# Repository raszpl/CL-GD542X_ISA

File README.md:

Fork of https://github.com/matt1187/542x_ISA 'Remaking from Cirrus Logic Databook "CL-GD542X_Technical_Reference_Manual_Jan1994"' attempting to show some routing optimizations.

# Results

Original:

Optimisations, less and taking smaller area tracks you see on the back means better signal integrity.

Initial:

Final:

Comparison between layouts: [Original](/images/original.png?raw=true), [Initial optimization](/images/first.png?raw=true), [Final version](/images/final.png?raw=true).

Black holes and red are cuts in ground plane, the smaller they are the better. Ideally you want one uninterrupted plane. Second bad but better than nothing option is ground island densely stitched on top of tracks forced to go into ground plane. Third bad option is as short as possible cuts to the ground plane and picking slow/steady (reset, VCC) signals as the ones going across, jumping across couple signals here and there is a lesser crime than slicing ground across half the PCB height. Fourth 'Im desperate here' option is crossing signals at 90 degree angle and hoping PCB thickness is enough. People in the eighties and early nineties didnt have it easy, nowadays similar size 4-layer PCBs are mere $20-30 for quick turnaround pototypes, with 6-layer not far behind at $40!

# Fixes

1 Bad ground. We dont want thin long ground noodles connected to real ground by a thin sliver on one side

like between:
- PD0 PD1 PD2 PD3 PD4 PD5 PD6
- PD16 20 21 22 23
- under U5
- tiny one under U11
- long big one under extended ISA slot
- A2_ISA 3 4 5 6 7

Ground that is not solid plane or densely (<wavelenght) stitched to solid plane no longer works as ground, it works like an antenna and amplifies interference. In the past guard traces were used before we had good modeling and understanding of magnetic propagation on the pcb, they only worked because putting one forced engineers to make more space between signal traces. All those dangling traces between signal tracks just resonate amplifying interference[^1].

3 Extended ISA slot - routing VCC straight to C33 instead of going across the card wouldnt be breaking ground plane under D8-16 and LA signals.

4 Omitting ISA oscillator input option will make ground more solid. Currently it leaves a dangling track with very high frequency clock crossing D8-18 and LA lines while breaking ground even when unused. Using ISA 14MHz was a cost cutting measure saving maybe 50 cents for a crystal resonator and two capacitors in the nineties, nowadays useless.

5 Pin 159 oscillator goes in a weird around pad way making it go outside of ground plane coverage. Its especially critical to have uninterrupted ground under clock signals.

6 Afaik separate isolated analog/digital ground planes is a relic of the past, modern techniques show it doesnt work if it cuts up ground into multiple islands and forces signals to cross them[^2][^3][^4]. Here for example it paradoxically messes with analog signal integrity by making RGB Video suddenly lose reference. Im fairly certain this aspect of Cirrus recommended design only makes things worse.

7 Optional EEprom pins also degrade analog RGB Video signals by breaking ground :( best option would be routing those two tracks with jumpers over analog RGB.

8 Filtering analog VGA looks nice when symmetricaly placed in neat rows, but forces analog B crossing over analog G, and all analog tracks going under where they arent routed over ground plane. Vias high impedance is really bad for such high speed analog signals. Asymmetrical component placement might hurt OCD, but lets us leave Analog RGB on top layer over healthy uninterrupted ground.

9 H and V syncs cross each other with no ground underneath, swapping filtering sections around solves that.

10 3 amp fuse and thick tracks on Vga Pin 9 is overdoing it, especially considering Cirrus is not even capable of reading Edid. Removing altogether.

11 Very long RAS1 under U13 U14 can be avoided, makes it look stupid but ground plane is healthier = shorter cuts = shorter return paths = less interference and crosstalk.

TLDR Golden rule is every signal should run as close as possible (preferably over) a ground directly connecting source and destination of said signal with lowest impedance. Signals arent electrons, they are electromagnetic waves and need to close the loop. Closer the ground smaller the field, lower the ground impedance higher the frequency of mitigated interferences, bigger ground plane = better, traveling thru multiple vias = bad.

Some of the fixes are heavily overdoing it via stitched ground patches and are most likely also bad :) Nowadays upgrading from five PCBs with 2-layers to 4-layers of that size is $20, another $15 for 6-layer with ENIG finish, giving us infinitely healthier signal integrity and tons less routing work. __Please dont manufacture this!__ Other than for fun or experimentation there is very little sense manufacturing 2-layer design, repository is for educational purposes only.

# License
The project is free for non-commercial reproduction. Do not sell it on Ebay or other platforms for profit. Do not make a closed source derivative. Share your experiences and ideas with the community.

This work is licensed under a [Creative Commons Attribution-NonCommercial-ShareAlike 4.0 International License][cc-by-nc-sa].

[![CC BY-NC-SA 4.0][cc-by-nc-sa-image]][cc-by-nc-sa]

[cc-by-nc-sa]: http://creativecommons.org/licenses/by-nc-sa/4.0/
[cc-by-nc-sa-image]: https://licensebuttons.net/l/by-nc-sa/4.0/88x31.png

# References
[^1]: https://resources.altium.com/p/guard-traces-hit-or-myth.
[^2]: https://resources.altium.com/p/how-to-use-a-star-point-for-analog-ground-digital-ground-connection
[^3]: https://resources.pcb.cadence.com/blog/2021-should-you-ever-separate-analog-and-digital-ground-planes
[^4]: "Ground planes in a PCB layout with 30 years of experience: The ultimate guide" by Hans Rosenberg https://www.youtube.com/watch?v=EEb_0dja8tE&list=PLsWHPs7La-3KUY2JDUyrz0Jc0xw8kH4zQ

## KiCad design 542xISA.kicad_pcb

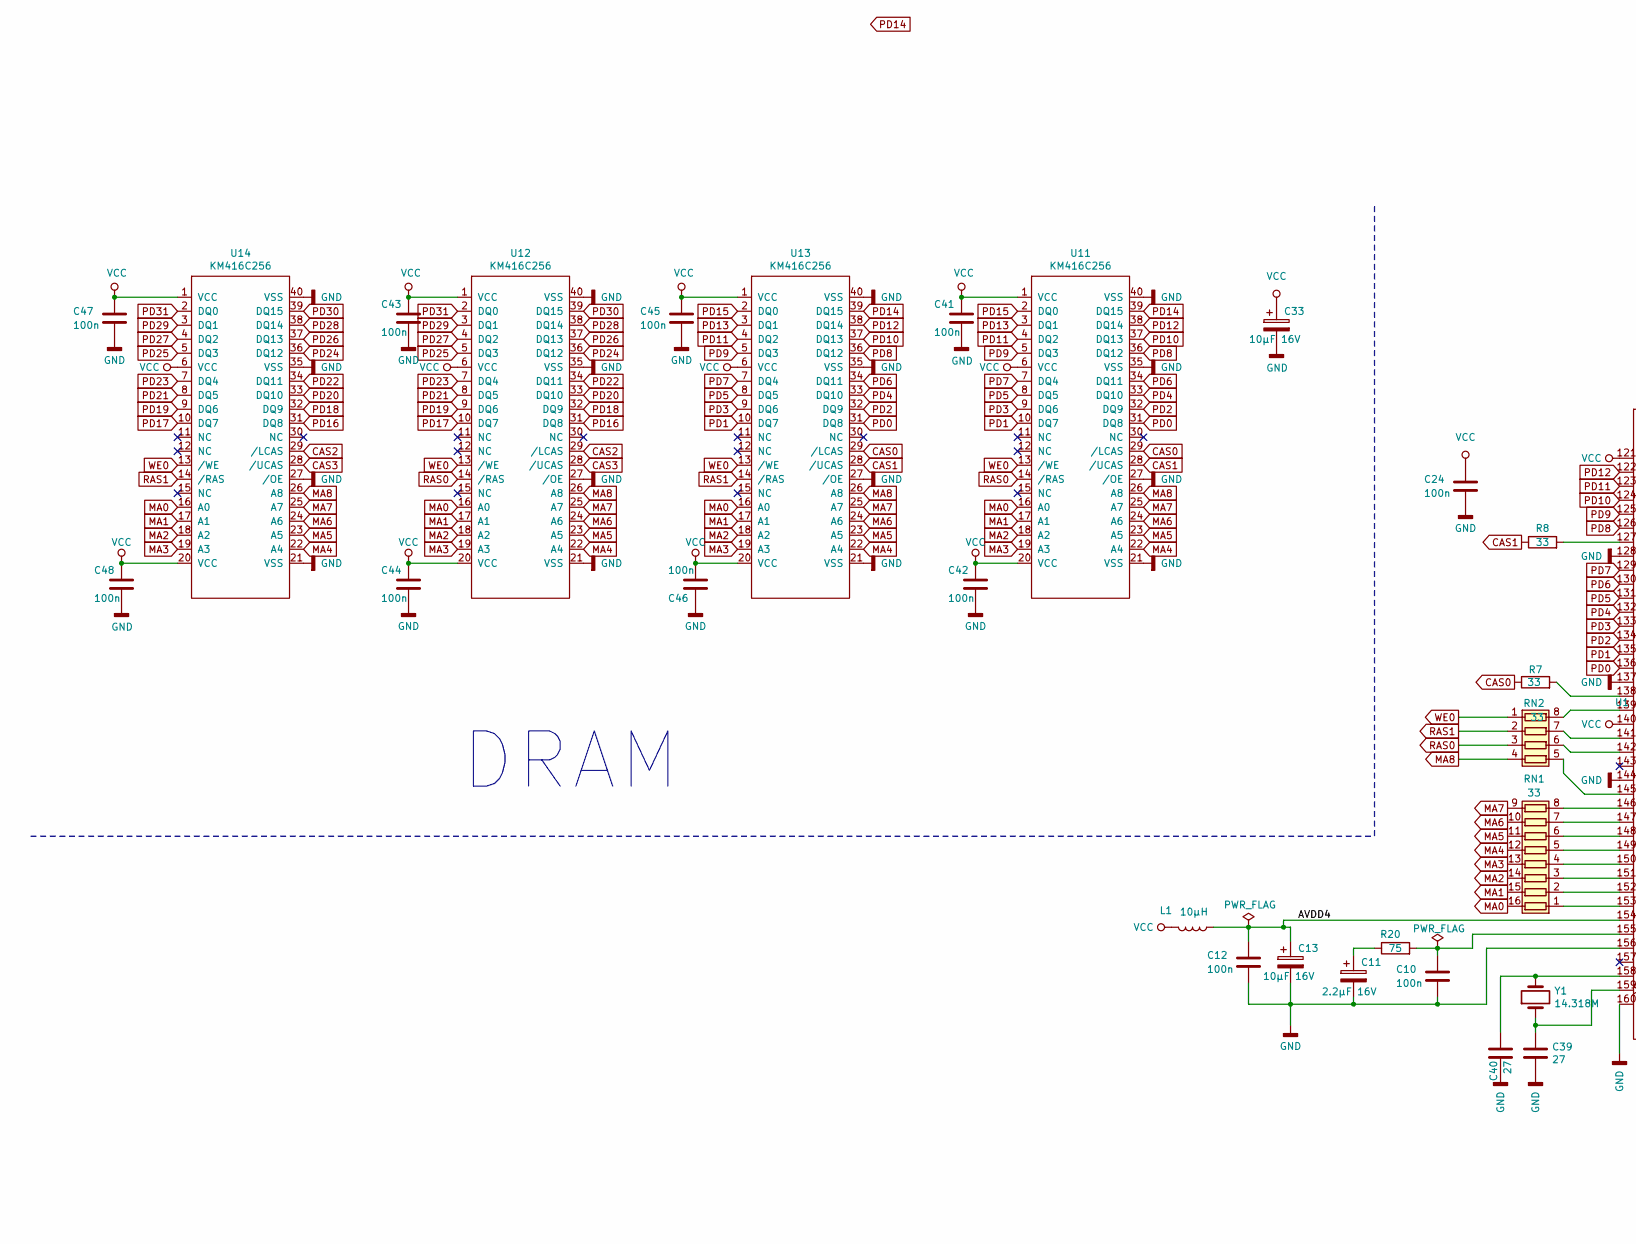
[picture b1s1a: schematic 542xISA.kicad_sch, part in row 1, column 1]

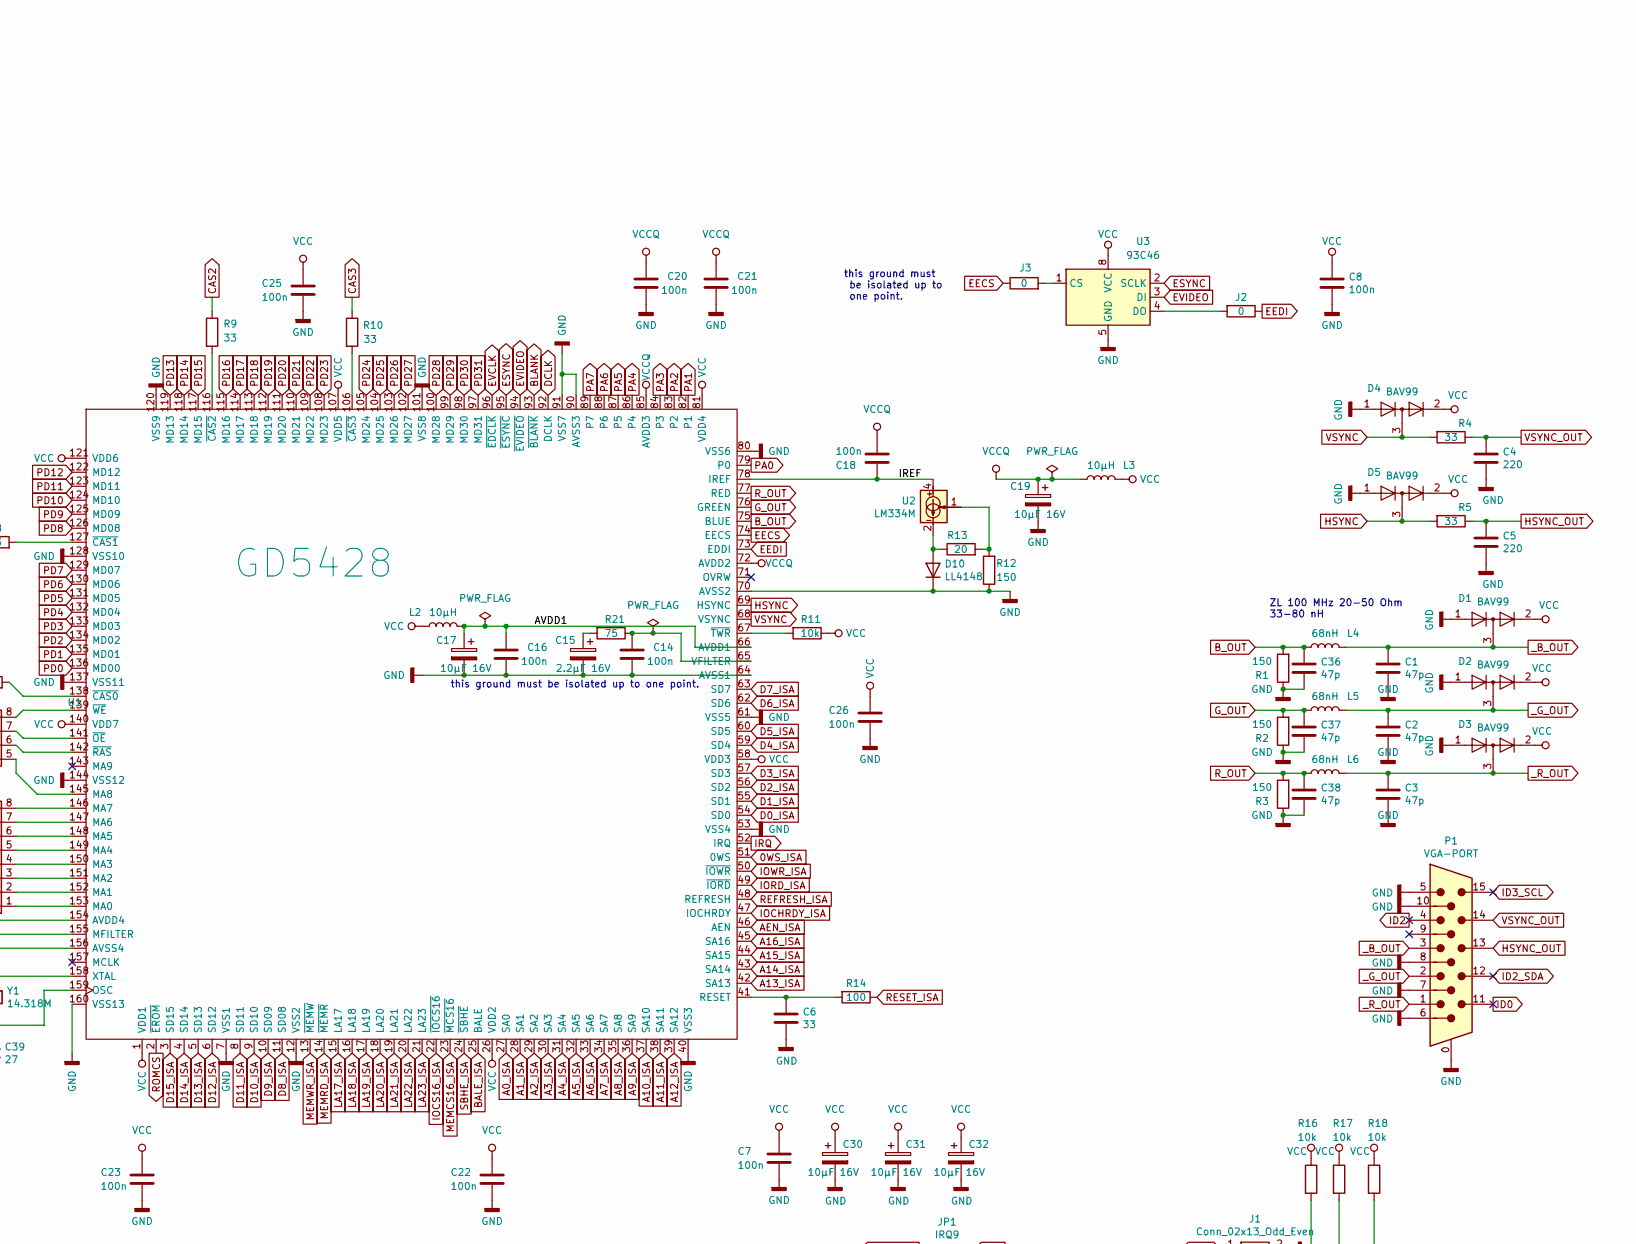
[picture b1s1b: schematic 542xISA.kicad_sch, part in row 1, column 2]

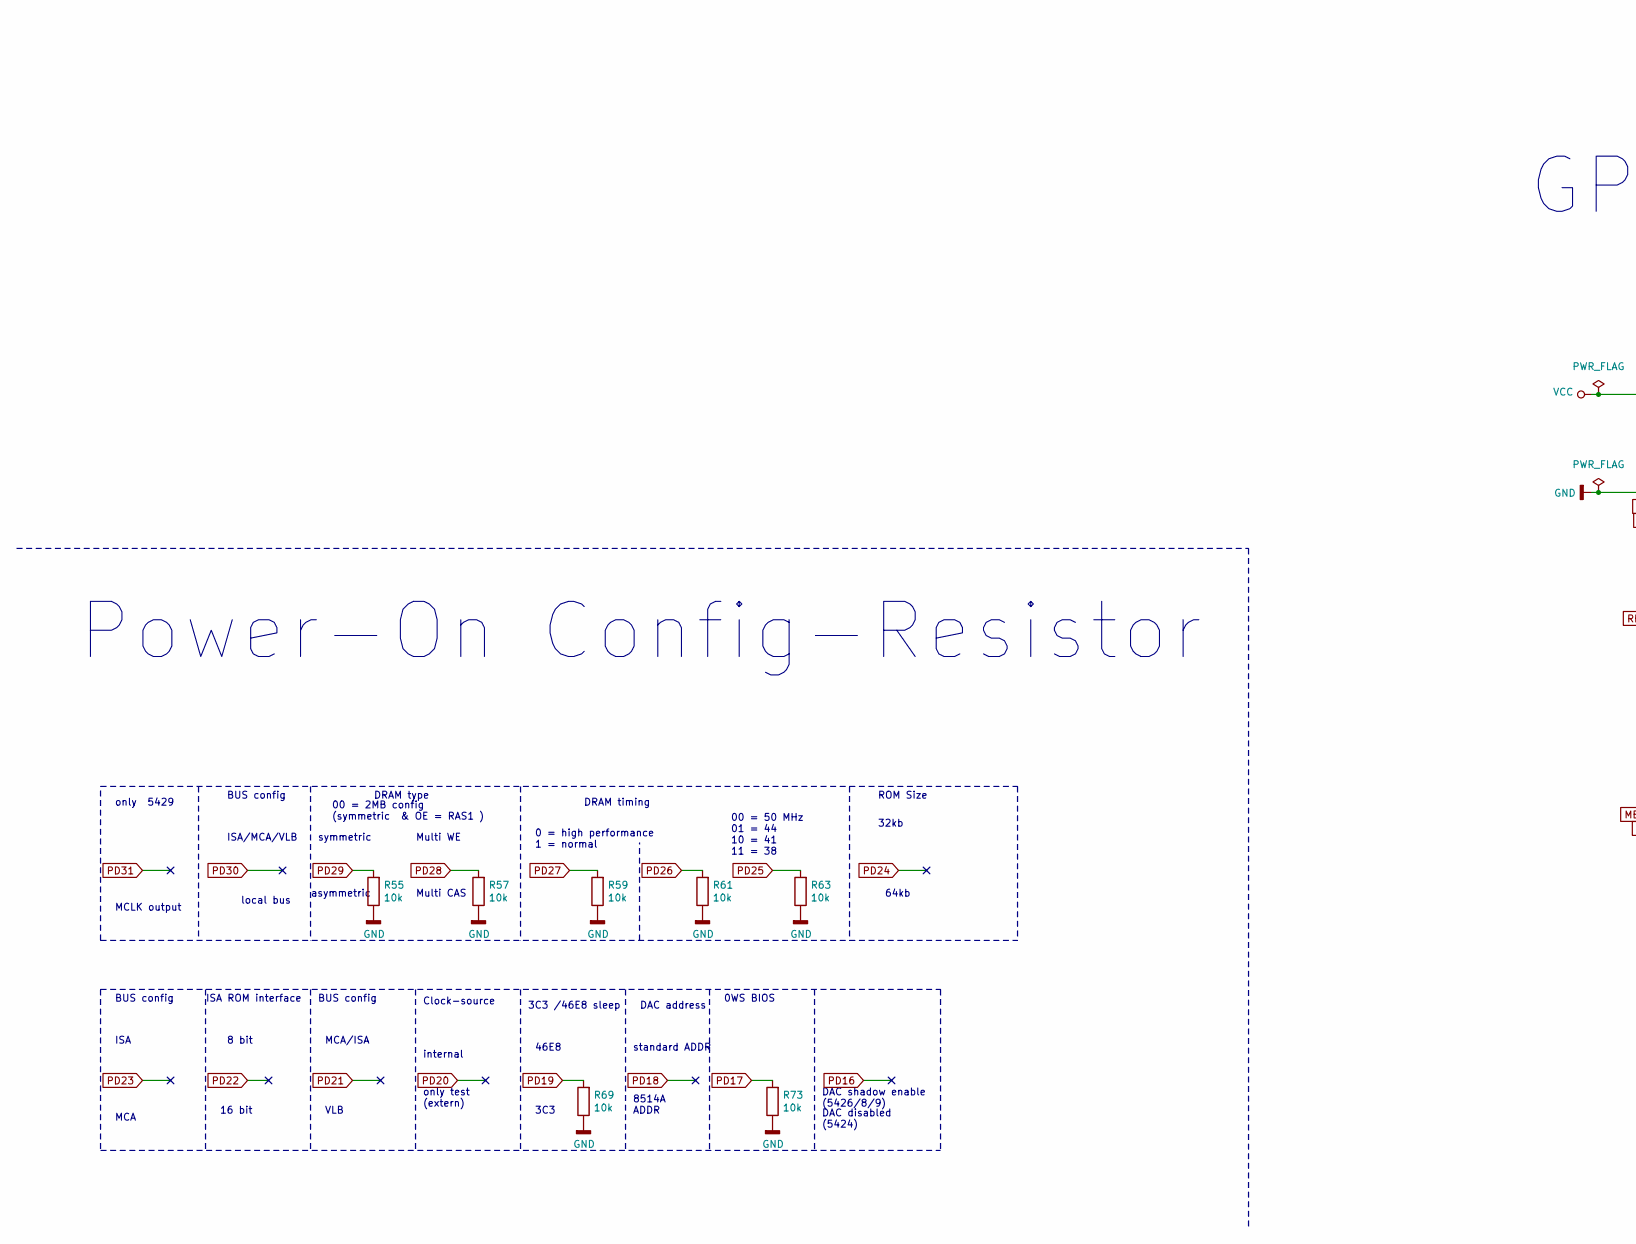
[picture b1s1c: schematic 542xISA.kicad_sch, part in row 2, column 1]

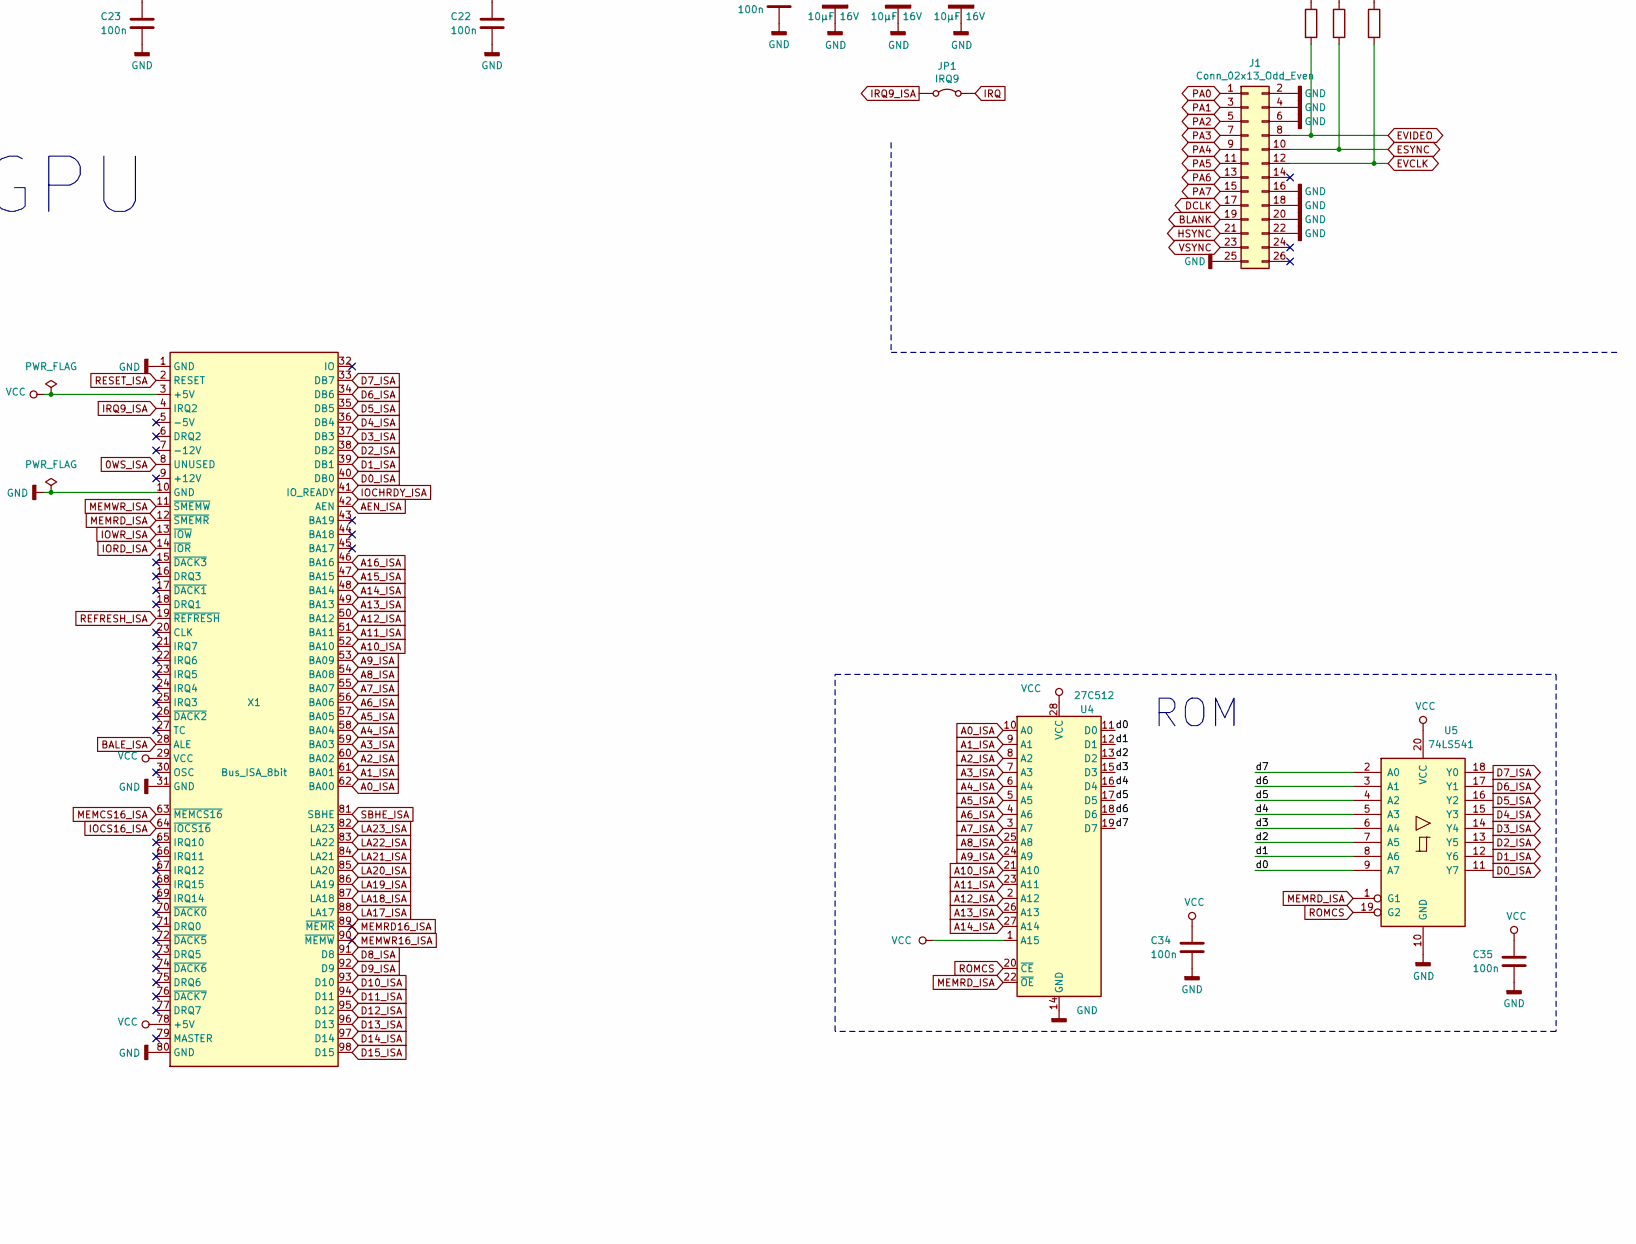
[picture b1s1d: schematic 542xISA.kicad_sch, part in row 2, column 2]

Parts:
C1, C2, C3, C36, C37, C38: 47p; C_0805_2012Metric
C4, C5: 220; C_0805_2012Metric
C6: 33; C_0805_2012Metric
C7, C8, C10, C12, C14, C16, C18, C20, C21, C22, C23, C24, C25, C26, C34, C35, C41, C42, C43, C44, C45, C46, C47, C48: 100n; C_0805_2012Metric
C11, C15: 2.2µF 16V; CP_EIA-3528-12_Kemet-T
C13, C17, C19, C30, C31, C32, C33: 10µF 16V; CP_EIA-6032-15_Kemet-U
C39, C40: 27; C_0805_2012Metric
D1, D2, D3, D4, D5: BAV99; SOT-23_Handsoldering
D10: LL4148; D_MiniMELF
J1: Conn_02x13_Odd_Even; PinHeader_2x13_P2.54mm_Vertical
J2, J3: 0; L_1806_4516Metric_Pad1.45x1.90mm_HandSolder
JP1: IRQ9; PinHeader_1x02_P2.54mm_Vertical
L1, L2: 10µH; L_0805_2012Metric
L3: 10µH; L_1206_3216Metric
L4, L5, L6: 68nH; L_1206_3216Metric
P1: VGA-PORT; DSUB-15-HD_Female_Horizontal_P2.29x1.98mm_EdgePinOffset8.35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
R1, R2, R3, R12: 150; R_0805_2012Metric
R4, R5, R7, R8, R9, R10: 33; R_0805_2012Metric
R11, R16, R17, R18, R55, R57, R59, R61, R63, R69, R73: 10k; R_0805_2012Metric
R13: 20; R_0805_2012Metric
R14: 100; R_0805_2012Metric
R20, R21: 75; R_0805_2012Metric
RN1: 33; R_Array_Convex_8x0602
RN2: 33; R_Array_Concave_4x0603
U1: GD5428; PQFP-160_28x28mm_P0.65mm
U2: LM334M; SOIC-8_3.9x4.9mm_P1.27mm
U3: 93C46; SOIC-8_3.9x4.9mm_P1.27mm
U4: 27C512; DIP-28_W15.24mm_Socket
U5: 74LS541; SOIC-20W_7.5x12.8mm_P1.27mm
U11, U12, U13, U14: KM416C256; SOJ-40-Socket-LongPads
X1: Bus_ISA_8bit; BUS_AT
Y1: 14.318M; Crystal_SMD_0603-2Pin_6.0x3.5mm

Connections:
0WS_ISA: U1.51 (0WS), X1.8 (UNUSED)
/AVDD1: C16.1, C17.1, L2.2, U1.66 (AVDD1)
/AVDD4: C12.1, C13.1, L1.1, U1.154 (AVDD4)
/IREF: C18.1, U1.78 (IREF), U2.4
/d0: U4.11 (D0), U5.9 (A7)
/d1: U4.12 (D1), U5.8 (A6)
/d2: U4.13 (D2), U5.7 (A5)
/d3: U4.15 (D3), U5.6 (A4)
/d4: U4.16 (D4), U5.5 (A3)
/d5: U4.17 (D5), U5.4 (A2)
/d6: U4.18 (D6), U5.3 (A1)
/d7: U4.19 (D7), U5.2 (A0)
A0_ISA: U1.27 (SA0), U4.10 (A0), X1.62 (BA00)
A1_ISA: U1.28 (SA1), U4.9 (A1), X1.61 (BA01)
A2_ISA: U1.29 (SA2), U4.8 (A2), X1.60 (BA02)
A3_ISA: U1.30 (SA3), U4.7 (A3), X1.59 (BA03)
A4_ISA: U1.31 (SA4), U4.6 (A4), X1.58 (BA04)
A5_ISA: U1.32 (SA5), U4.5 (A5), X1.57 (BA05)
A6_ISA: U1.33 (SA6), U4.4 (A6), X1.56 (BA06)
A7_ISA: U1.34 (SA7), U4.3 (A7), X1.55 (BA07)
A8_ISA: U1.35 (SA8), U4.25 (A8), X1.54 (BA08)
A9_ISA: U1.36 (SA9), U4.24 (A9), X1.53 (BA09)
A10_ISA: U1.37 (SA10), U4.21 (A10), X1.52 (BA10)
A11_ISA: U1.38 (SA11), U4.23 (A11), X1.51 (BA11)
A12_ISA: U1.39 (SA12), U4.2 (A12), X1.50 (BA12)
A13_ISA: U1.42 (SA13), U4.26 (A13), X1.49 (BA13)
A14_ISA: U1.43 (SA14), U4.27 (A14), X1.48 (BA14)
A15_ISA: U1.44 (SA15), X1.47 (BA15)
A16_ISA: U1.45 (SA16), X1.46 (BA16)
AEN_ISA: U1.46 (AEN), X1.42 (AEN)
BALE_ISA: U1.25 (BALE), X1.28 (ALE)
BLANK: J1.19, U1.93 (~BLANK)
B_OUT: C36.1, L4.2, R1.2, U1.75 (BLUE)
CAS0: R7.1, U11.29 (/LCAS), U13.29 (/LCAS)
CAS1: R8.1, U11.28 (/UCAS), U13.28 (/UCAS)
CAS2: R9.1, U12.29 (/LCAS), U14.29 (/LCAS)
CAS3: R10.1, U12.28 (/UCAS), U14.28 (/UCAS)
D0_ISA: U1.54 (SD0), U5.11 (Y7), X1.40 (DB0)
D1_ISA: U1.55 (SD1), U5.12 (Y6), X1.39 (DB1)
D2_ISA: U1.56 (SD2), U5.13 (Y5), X1.38 (DB2)
D3_ISA: U1.57 (SD3), U5.14 (Y4), X1.37 (DB3)
D4_ISA: U1.59 (SD4), U5.15 (Y3), X1.36 (DB4)
D5_ISA: U1.60 (SD5), U5.16 (Y2), X1.35 (DB5)
D6_ISA: U1.62 (SD6), U5.17 (Y1), X1.34 (DB6)
D7_ISA: U1.63 (SD7), U5.18 (Y0), X1.33 (DB7)
D8_ISA: U1.11 (SD08), X1.91 (D8)
D9_ISA: U1.10 (SD09), X1.92 (D9)
D10_ISA: U1.9 (SD10), X1.93 (D10)
D11_ISA: U1.8 (SD11), X1.94 (D11)
D12_ISA: U1.6 (SD12), X1.95 (D12)
D13_ISA: U1.5 (SD13), X1.96 (D13)
D14_ISA: U1.4 (SD14), X1.97 (D14)
D15_ISA: U1.3 (SD15), X1.98 (D15)
DCLK: J1.17, U1.92 (DCLK)
EECS: J3.1, U1.74 (EECS)
EEDI: J2.1, U1.73 (EDDI)
ESYNC: J1.10, R17.2, U1.95 (~ESYNC), U3.2 (SCLK)
EVCLK: J1.12, R18.2, U1.96 (~EDCLK)
EVIDEO: J1.8, R16.2, U1.94 (~EVIDEO), U3.3 (DI)
GND: C1.2, C2.2, C3.2, C4.2, C5.2, C6.2, C7.2, C8.2, C10.2, C11.2, C12.2, C13.2, C14.2, C15.2, C16.2, C17.2, C19.2, C20.2, C21.2, C22.2, C23.2, C24.2, C25.2, C26.2, C30.2, C31.2, C32.2, C33.2, C34.2, C35.2, C36.2, C37.2, C38.2, C39.2, C40.1, C41.2, C42.2, C43.2, C44.2, C45.2, C46.2, C47.2, C48.2, D1.1 (K), D2.1 (K), D3.1 (K), D4.1 (K), D5.1 (K), D10.1 (K), J1.2, J1.4, J1.6, J1.16, J1.18, J1.20, J1.22, J1.25, P1.0, P1.5, P1.6, P1.7, P1.8, P1.10, R1.1, R2.1, R3.1, R12.1, R55.1, R57.1, R59.1, R61.1, R63.1, R69.1, R73.1, U1.7 (VSS1), U1.12 (VSS2), U1.40 (VSS3), U1.53 (VSS4), U1.61 (VSS5), U1.64 (AVSS1), U1.70 (AVSS2), U1.80 (VSS6), U1.90 (AVSS3), U1.91 (VSS7), U1.101 (VSS8), U1.120 (VSS9), U1.128 (VSS10), U1.137 (VSS11), U1.144 (VSS12), U1.156 (AVSS4), U1.160 (VSS13), U3.5 (GND), U4.14 (GND), U5.10 (GND), U11.21 (VSS), U11.27 (/OE), U11.35 (VSS), U11.40 (VSS), U12.21 (VSS), U12.27 (/OE), U12.35 (VSS), U12.40 (VSS), U13.21 (VSS), U13.27 (/OE), U13.35 (VSS), U13.40 (VSS), U14.21 (VSS), U14.27 (/OE), U14.35 (VSS), U14.40 (VSS), X1.1 (GND), X1.10 (GND), X1.31 (GND), X1.80 (GND)
G_OUT: C37.1, L5.2, R2.2, U1.76 (GREEN)
HSYNC: D5.3 (K), J1.21, R5.2, U1.69 (HSYNC)
HSYNC_OUT: C5.1, P1.13, R5.1
ID0: P1.11
ID2: P1.4
ID2_SDA: P1.12
ID3_SCL: P1.15
IOCHRDY_ISA: U1.47 (IOCHRDY), X1.41 (IO_READY)
IOCS16_ISA: U1.22 (~IOCS16), X1.64 (~IOCS16)
IORD_ISA: U1.49 (~IORD), X1.14 (~IOR)
IOWR_ISA: U1.50 (~IOWR), X1.13 (~IOW)
IRQ: JP1.2 (B), U1.52 (IRQ)
IRQ9_ISA: JP1.1 (A), X1.4 (IRQ2)
LA17_ISA: U1.15 (LA17), X1.88 (LA17)
LA18_ISA: U1.16 (LA18), X1.87 (LA18)
LA19_ISA: U1.17 (LA19), X1.86 (LA19)
LA20_ISA: U1.18 (LA20), X1.85 (LA20)
LA21_ISA: U1.19 (LA21), X1.84 (LA21)
LA22_ISA: U1.20 (LA22), X1.83 (LA22)
LA23_ISA: U1.21 (LA23), X1.82 (LA23)
MA0: RN1.16 (R1.2), U11.16 (A0), U12.16 (A0), U13.16 (A0), U14.16 (A0)
MA1: RN1.15 (R2.2), U11.17 (A1), U12.17 (A1), U13.17 (A1), U14.17 (A1)
MA2: RN1.14 (R3.2), U11.18 (A2), U12.18 (A2), U13.18 (A2), U14.18 (A2)
MA3: RN1.13 (R4.2), U11.19 (A3), U12.19 (A3), U13.19 (A3), U14.19 (A3)
MA4: RN1.12 (R5.2), U11.22 (A4), U12.22 (A4), U13.22 (A4), U14.22 (A4)
MA5: RN1.11 (R6.2), U11.23 (A5), U12.23 (A5), U13.23 (A5), U14.23 (A5)
MA6: RN1.10 (R7.2), U11.24 (A6), U12.24 (A6), U13.24 (A6), U14.24 (A6)
MA7: RN1.9 (R8.2), U11.25 (A7), U12.25 (A7), U13.25 (A7), U14.25 (A7)
MA8: RN2.4 (R4.1), U11.26 (A8), U12.26 (A8), U13.26 (A8), U14.26 (A8)
MEMCS16_ISA: U1.23 (~MCS16), X1.63 (~MEMCS16)
MEMRD16_ISA: X1.89 (~MEMR)
MEMRD_ISA: U1.14 (~MEMR), U4.22 (~OE), U5.1 (G1), X1.12 (~SMEMR)
MEMWR16_ISA: X1.90 (~MEMW)
MEMWR_ISA: U1.13 (~MEMW), X1.11 (~SMEMW)
unnamed: C11.1, R20.1
unnamed: C15.1, R21.2
unnamed: D10.2 (A), R13.1, U2.2, U2.3, U2.6, U2.7
unnamed: R12.2, R13.2, U2.1
unnamed: RN1.1 (R1.1), U1.153 (MA0)
unnamed: RN1.2 (R2.1), U1.152 (MA1)
unnamed: RN1.3 (R3.1), U1.151 (MA2)
unnamed: RN1.4 (R4.1), U1.150 (MA3)
unnamed: RN1.5 (R5.1), U1.149 (MA4)
unnamed: RN1.6 (R6.1), U1.148 (MA5)
unnamed: RN1.7 (R7.1), U1.147 (MA6)
unnamed: RN1.8 (R8.1), U1.146 (MA7)
unnamed: RN2.8 (R1.2), U1.139 (~WE)
unnamed: RN2.7 (R2.2), U1.141 (~OE)
unnamed: RN2.6 (R3.2), U1.142 (~RAS)
unnamed: RN2.5 (R4.2), U1.145 (MA8)
unnamed: C10.1, R20.2, U1.155 (MFILTER)
unnamed: C39.1, U1.159 (OSC), Y1.1
unnamed: C6.1, R14.2, U1.41 (RESET)
unnamed: C14.1, R21.1, U1.65 (VFILTER)
unnamed: C40.2, U1.158 (XTAL), Y1.2
unnamed: R7.2, U1.138 (~CAS0)
unnamed: R8.2, U1.127 (~CAS1)
unnamed: R9.2, U1.116 (~CAS2)
unnamed: R10.2, U1.106 (~CAS3)
unnamed: R11.2, U1.67 (~TWR)
unnamed: J3.2, U3.1 (CS)
unnamed: J2.2, U3.4 (DO)
PA0: J1.1, U1.79 (P0)
PA1: J1.3, U1.82 (P1)
PA2: J1.5, U1.83 (P2)
PA3: J1.7, U1.84 (P3)
PA4: J1.9, U1.86 (P4)
PA5: J1.11, U1.87 (P5)
PA6: J1.13, U1.88 (P6)
PA7: J1.15, U1.89 (P7)
PD0: U1.136 (MD00), U11.31 (DQ8), U13.31 (DQ8)
PD1: U1.135 (MD01), U11.10 (DQ7), U13.10 (DQ7)
PD2: U1.134 (MD02), U11.32 (DQ9), U13.32 (DQ9)
PD3: U1.133 (MD03), U11.9 (DQ6), U13.9 (DQ6)
PD4: U1.132 (MD04), U11.33 (DQ10), U13.33 (DQ10)
PD5: U1.131 (MD05), U11.8 (DQ5), U13.8 (DQ5)
PD6: U1.130 (MD06), U11.34 (DQ11), U13.34 (DQ11)
PD7: U1.129 (MD07), U11.7 (DQ4), U13.7 (DQ4)
PD8: U1.126 (MD08), U11.36 (DQ12), U13.36 (DQ12)
PD9: U1.125 (MD09), U11.5 (DQ3), U13.5 (DQ3)
PD10: U1.124 (MD10), U11.37 (DQ13), U13.37 (DQ13)
PD11: U1.123 (MD11), U11.4 (DQ2), U13.4 (DQ2)
PD12: U1.122 (MD12), U11.38 (DQ14), U13.38 (DQ14)
PD13: U1.119 (MD13), U11.3 (DQ1), U13.3 (DQ1)
PD14: U1.118 (MD14), U11.39 (DQ15), U13.39 (DQ15)
PD15: U1.117 (MD15), U11.2 (DQ0), U13.2 (DQ0)
PD16: U1.115 (MD16), U12.31 (DQ8), U14.31 (DQ8)
PD17: R73.2, U1.114 (MD17), U12.10 (DQ7), U14.10 (DQ7)
PD18: U1.113 (MD18), U12.32 (DQ9), U14.32 (DQ9)
PD19: R69.2, U1.112 (MD19), U12.9 (DQ6), U14.9 (DQ6)
PD20: U1.111 (MD20), U12.33 (DQ10), U14.33 (DQ10)
PD21: U1.110 (MD21), U12.8 (DQ5), U14.8 (DQ5)
PD22: U1.109 (MD22), U12.34 (DQ11), U14.34 (DQ11)
PD23: U1.108 (MD23), U12.7 (DQ4), U14.7 (DQ4)
PD24: U1.105 (MD24), U12.36 (DQ12), U14.36 (DQ12)
PD25: R63.2, U1.104 (MD25), U12.5 (DQ3), U14.5 (DQ3)
PD26: R61.2, U1.103 (MD26), U12.37 (DQ13), U14.37 (DQ13)
PD27: R59.2, U1.102 (MD27), U12.4 (DQ2), U14.4 (DQ2)
PD28: R57.2, U1.100 (MD28), U12.38 (DQ14), U14.38 (DQ14)
PD29: R55.2, U1.99 (MD29), U12.3 (DQ1), U14.3 (DQ1)
PD30: U1.98 (MD30), U12.39 (DQ15), U14.39 (DQ15)
PD31: U1.97 (MD31), U12.2 (DQ0), U14.2 (DQ0)
RAS0: RN2.3 (R3.1), U11.14 (/RAS), U12.14 (/RAS)
RAS1: RN2.2 (R2.1), U13.14 (/RAS), U14.14 (/RAS)
REFRESH_ISA: U1.48 (REFRESH), X1.19 (~REFRESH)
RESET_ISA: R14.1, X1.2 (RESET)
ROMCS: U1.2 (~EROM), U4.20 (~CE), U5.19 (G2)
R_OUT: C38.1, L6.2, R3.2, U1.77 (RED)
SBHE_ISA: U1.24 (~SBHE), X1.81 (SBHE)
VCC: C7.1, C8.1, C22.1, C23.1, C24.1, C25.1, C26.1, C30.1, C31.1, C32.1, C33.1, C34.1, C35.1, C41.1, C42.1, C43.1, C44.1, C45.1, C46.1, C47.1, C48.1, D1.2 (A), D2.2 (A), D3.2 (A), D4.2 (A), D5.2 (A), L1.2, L2.1, L3.1, R11.1, R16.1, R17.1, R18.1, U1.1 (VDD1), U1.26 (VDD2), U1.58 (VDD3), U1.81 (VDD4), U1.107 (VDD5), U1.121 (VDD6), U1.140 (VDD7), U3.8 (VCC), U4.1 (A15), U4.28 (VCC), U5.20 (VCC), U11.1 (VCC), U11.6 (VCC), U11.20 (VCC), U12.1 (VCC), U12.6 (VCC), U12.20 (VCC), U13.1 (VCC), U13.6 (VCC), U13.20 (VCC), U14.1 (VCC), U14.6 (VCC), U14.20 (VCC), X1.3 (+5V), X1.29 (VCC), X1.78 (+5V)
VCCQ: C18.2, C19.1, C20.1, C21.1, L3.2, U1.72 (AVDD2), U1.85 (AVDD3)
VSYNC: D4.3 (K), J1.23, R4.2, U1.68 (VSYNC)
VSYNC_OUT: C4.1, P1.14, R4.1
WE0: RN2.1 (R1.1), U11.13 (/WE), U12.13 (/WE), U13.13 (/WE), U14.13 (/WE)
_B_OUT: C1.1, D1.3 (K), L4.1, P1.3
_G_OUT: C2.1, D2.3 (K), L5.1, P1.2
_R_OUT: C3.1, D3.3 (K), L6.1, P1.1

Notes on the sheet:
standard ADDR
DAC disabled (5424)
8 bit
DRAM
ISA/MCA/VLB
8514A ADDR
VLB
00 = 50 MHz 01 = 44 10 = 41 11 = 38
BUS config
MCLK output
Multi CAS
16 bit
MCA/ISA
32kb
Clock-source
ISA
GPU
DRAM timing
symmetric
only test (extern)
DAC address
Power-On Config-Resistor
this ground must be isolated up to one point.
64kb
3C3 /46E8 sleep
46E8
MCA
DAC shadow enable (5426/8/9)
only 5429
00 = 2MB config (symmetric & OE = RAS1 )
DRAM type
this ground must be isolated up to one point.
ROM
local bus
ZL 100 MHz 20-50 Ohm 33-80 nH
3C3
asymmetric
Multi WE
ISA ROM interface
0 = high performance 1 = normal

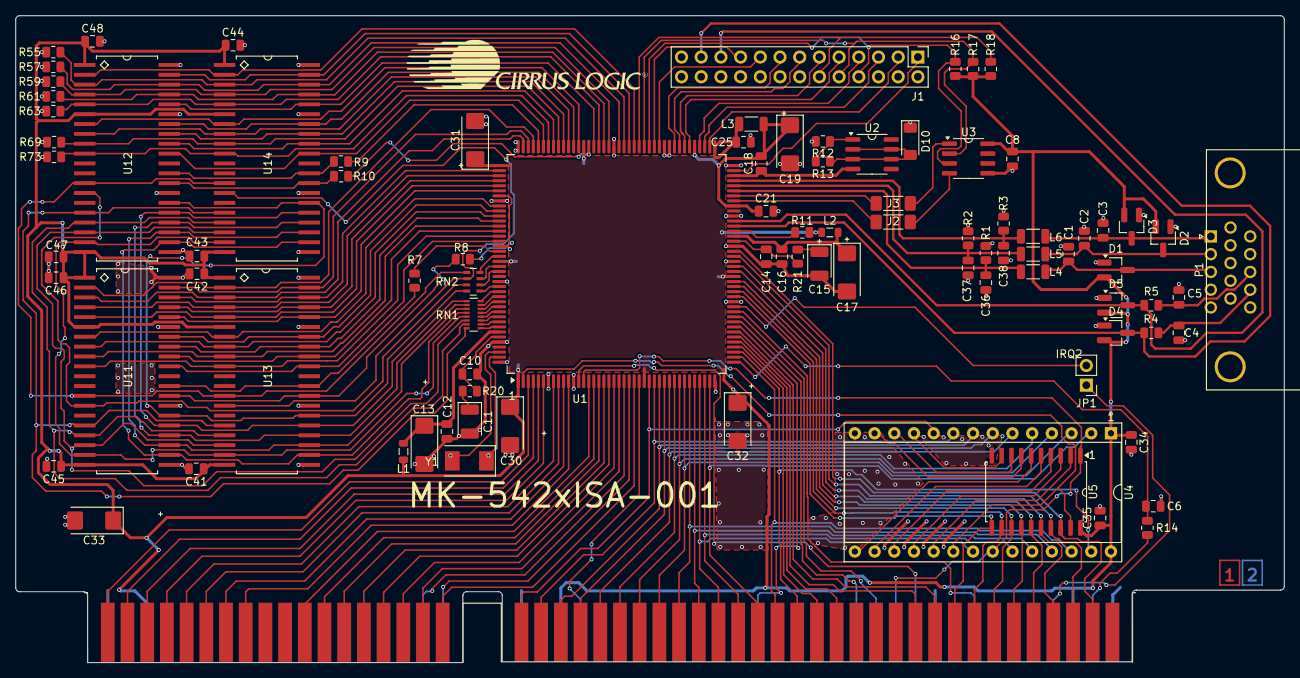
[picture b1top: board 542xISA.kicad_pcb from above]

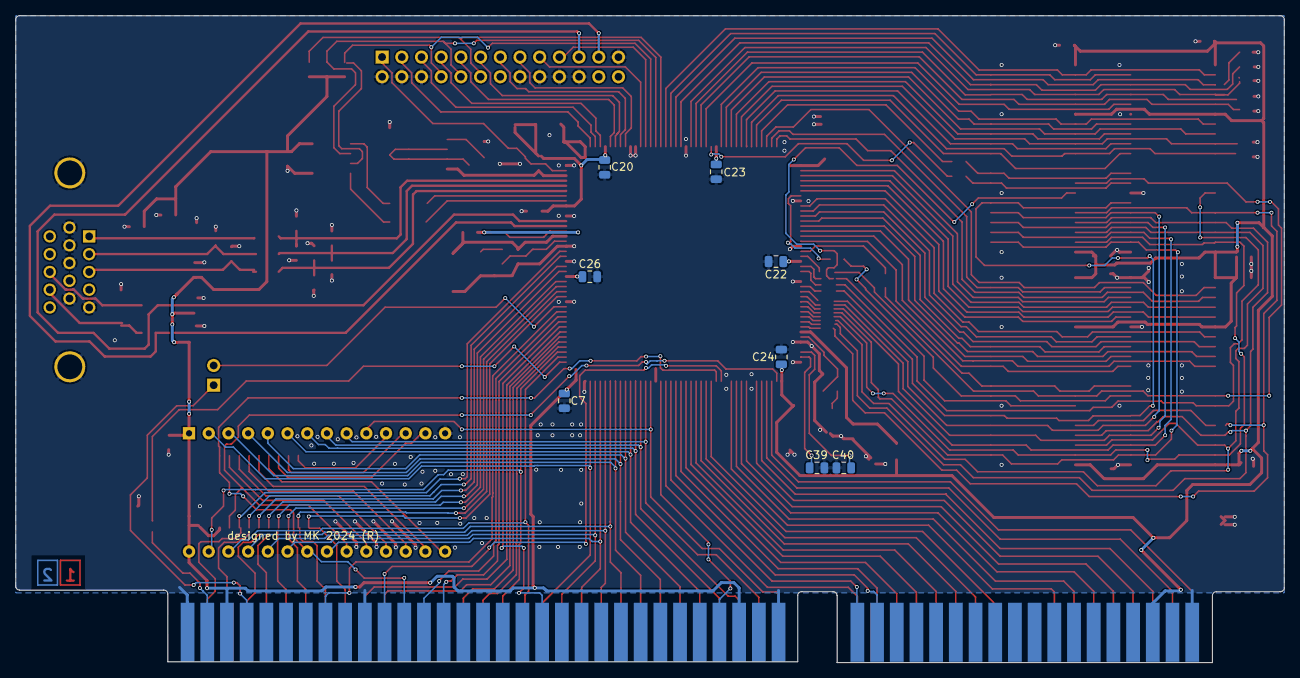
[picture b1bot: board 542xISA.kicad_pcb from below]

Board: 2 copper layers, 163.6 x 83.4 mm, 99 parts (8 on the bottom side), 171 nets.

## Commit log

2024-12-14 initial fork
2024-12-14 Rename bad_gnd1.png to images/bad_gnd1.png
2024-12-14 Rename bad_gnd2.png to images/bad_gnd2.png
2024-12-14 references
2024-12-14 0 ERC, 0 DRC errors.
2024-12-15 final version
2024-12-15 final comparison
2024-12-15 final writeup
2024-12-15 typos
